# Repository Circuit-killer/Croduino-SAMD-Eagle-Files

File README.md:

# Croduino SAMD Eagle Files
## Image
will be available soon

## Description and details
Arduino compatible board based on ATSAMD21G18J with native USB. 

## Repository content
This repo contains Cadsoft Eagle .sch and .brd files for Croduino SAMD board. It also contains schematic in .pdf created from .sch Eagle file. 
Files have been arranged into folders for navigating between different versions of board. 
Tip: layer 200 shows top silkscreen and layer 208 should be bottom silkscreen. tParts and bParts layers are not used in actual PCB. 

## Docs
- available soon

## Board versions
- v1.0 - inital published version 

## License info
This product is open-source. Yay!
For any tech questions, contact us at techsupport@e-radionica.com
If you find an Issue, please open one at GitHub. If you can improve our product, fork us.

e-radionica.com Team.

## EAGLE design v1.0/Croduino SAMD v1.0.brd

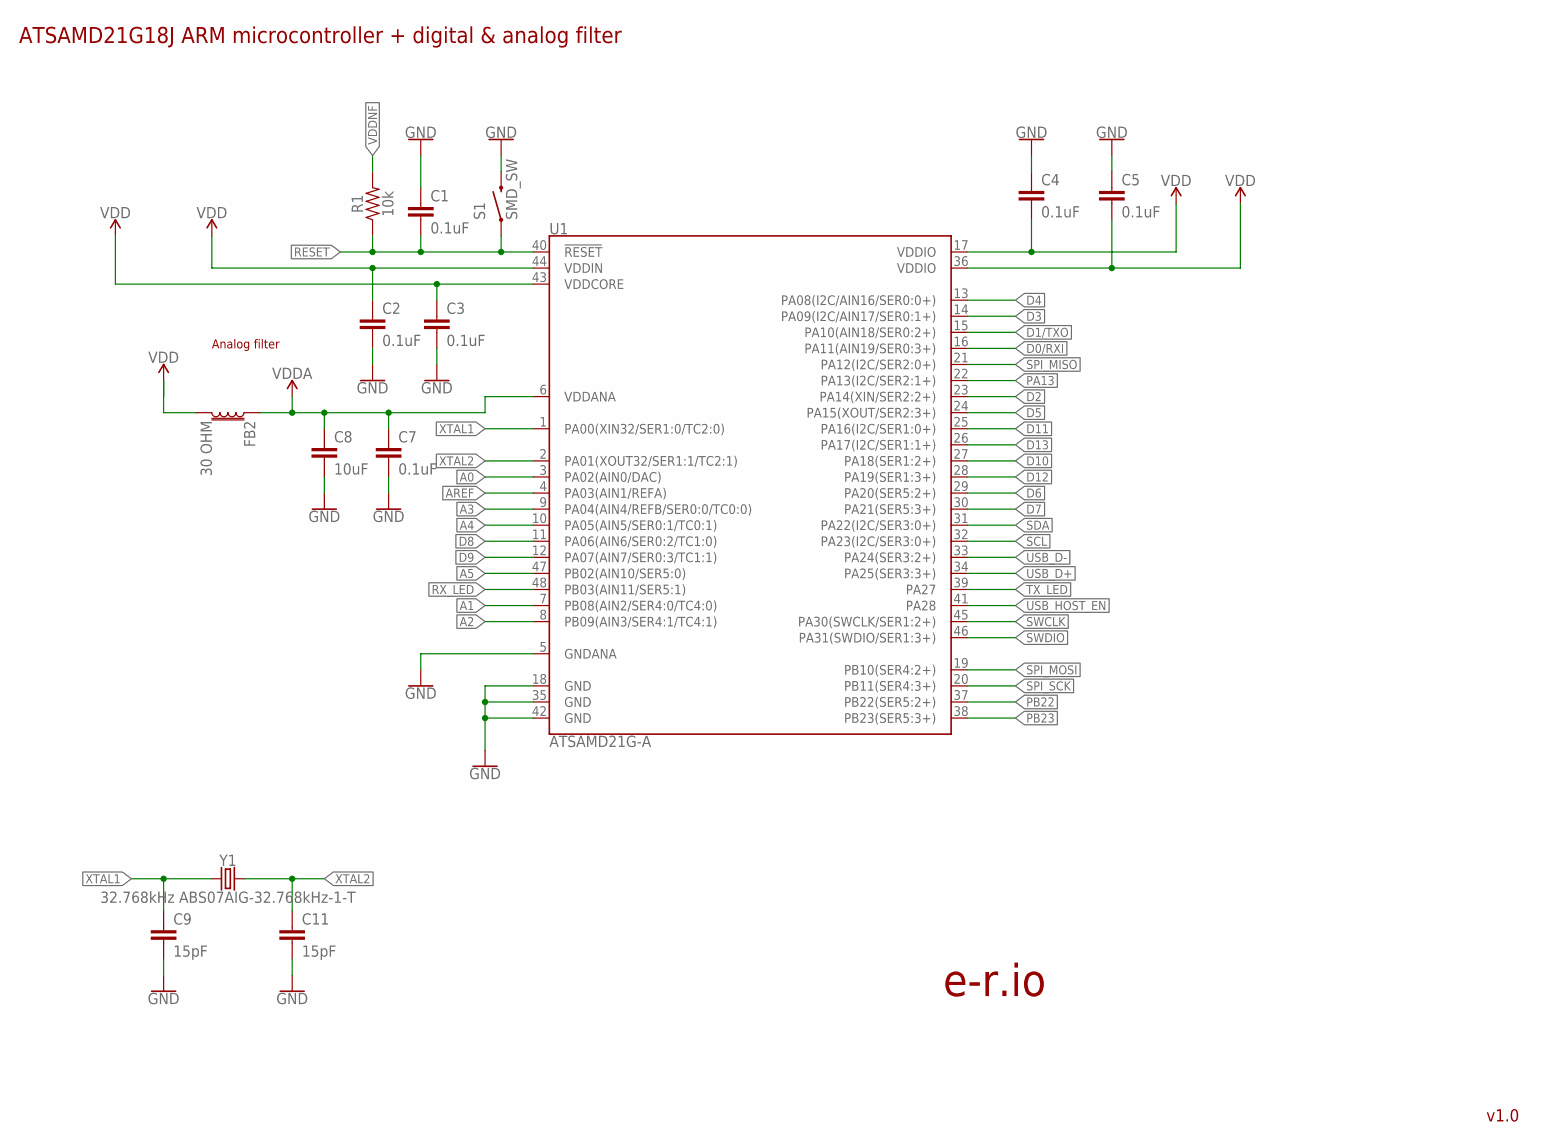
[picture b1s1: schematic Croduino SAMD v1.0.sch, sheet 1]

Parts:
C1, C2, C3, C4, C5, C7: 0.1uF; 0603
C8: 10uF; 1206
C9, C11: 15pF; 0603
FB2: 30 OHM; 0603
R1: 10k; 0603
S1: SMD_SW; TACTILE_SWITCH_SMD
U1: ATSAMD21G-A; TQFP-48
Y1: 32.768kHz ABS07AIG-32.768kHz-1-T; CRYSTAL-SMD-3.2X1.5MM

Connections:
A0: U1.3 (PA02(AIN0/DAC)); also elsewhere on the board
A1: U1.7 (PB08(AIN2/SER4:0/TC4:0)); also elsewhere on the board
A2: U1.8 (PB09(AIN3/SER4:1/TC4:1)); also elsewhere on the board
A3: U1.9 (PA04(AIN4/REFB/SER0:0/TC0:0)); also elsewhere on the board
A4: U1.10 (PA05(AIN5/SER0:1/TC0:1)); also elsewhere on the board
A5: U1.47 (PB02(AIN10/SER5:0)); also elsewhere on the board
AREF: U1.4 (PA03(AIN1/REFA)); also elsewhere on the board
D0/RXI: U1.16 (PA11(AIN19/SER0:3+)); also elsewhere on the board
D1/TXO: U1.15 (PA10(AIN18/SER0:2+)); also elsewhere on the board
D2: U1.23 (PA14(XIN/SER2:2+)); also elsewhere on the board
D3: U1.14 (PA09(I2C/AIN17/SER0:1+)); also elsewhere on the board
D4: U1.13 (PA08(I2C/AIN16/SER0:0+)); also elsewhere on the board
D5: U1.24 (PA15(XOUT/SER2:3+)); also elsewhere on the board
D6: U1.29 (PA20(SER5:2+)); also elsewhere on the board
D7: U1.30 (PA21(SER5:3+)); also elsewhere on the board
D8: U1.11 (PA06(AIN6/SER0:2/TC1:0)); also elsewhere on the board
D9: U1.12 (PA07(AIN7/SER0:3/TC1:1)); also elsewhere on the board
D10: U1.27 (PA18(SER1:2+)); also elsewhere on the board
D11: U1.25 (PA16(I2C/SER1:0+)); also elsewhere on the board
D12: U1.28 (PA19(SER1:3+)); also elsewhere on the board
D13: U1.26 (PA17(I2C/SER1:1+)); also elsewhere on the board
GND: C1.1, C2.2, C3.2, C4.1, C5.1, C7.2, C8.2, C9.2, C11.2, S1.3 (2), U1.5 (GNDANA), U1.18 (GND), U1.35 (GND), U1.42 (GND); also elsewhere on the board
PA13: U1.22 (PA13(I2C/SER2:1+)); also elsewhere on the board
PB22: U1.37 (PB22(SER5:2+)); also elsewhere on the board
PB23: U1.38 (PB23(SER5:3+)); also elsewhere on the board
RESET: C1.2, R1.1, S1.1, U1.40 (!RESET!); also elsewhere on the board
RX_LED: U1.48 (PB03(AIN11/SER5:1)); also elsewhere on the board
SCL: U1.32 (PA23(I2C/SER3:0+)); also elsewhere on the board
SDA: U1.31 (PA22(I2C/SER3:0+)); also elsewhere on the board
SPI_MISO: U1.21 (PA12(I2C/SER2:0+)); also elsewhere on the board
SPI_MOSI: U1.19 (PB10(SER4:2+)); also elsewhere on the board
SPI_SCK: U1.20 (PB11(SER4:3+)); also elsewhere on the board
SWCLK: U1.45 (PA30(SWCLK/SER1:2+)); also elsewhere on the board
SWDIO: U1.46 (PA31(SWDIO/SER1:3+)); also elsewhere on the board
TX_LED: U1.39 (PA27); also elsewhere on the board
USB_D+: U1.34 (PA25(SER3:3+)); also elsewhere on the board
USB_D-: U1.33 (PA24(SER3:2+)); also elsewhere on the board
USB_HOST_EN: U1.41 (PA28); also elsewhere on the board
VDD: C2.1, C3.1, C4.2, C5.2, FB2.2, U1.17 (VDDIO), U1.36 (VDDIO), U1.43 (VDDCORE), U1.44 (VDDIN); also elsewhere on the board
VDDA: C7.1, C8.1, FB2.1, U1.6 (VDDANA)
VDDNF: R1.2
XTAL1: C9.1, U1.1 (PA00(XIN32/SER1:0/TC2:0)), Y1.P$1 (1)
XTAL2: C11.1, U1.2 (PA01(XOUT32/SER1:1/TC2:1)), Y1.P$2 (2)

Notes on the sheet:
Analog filter
ATSAMD21G18J ARM microcontroller + digital & analog filter
e-r.io
v1.0

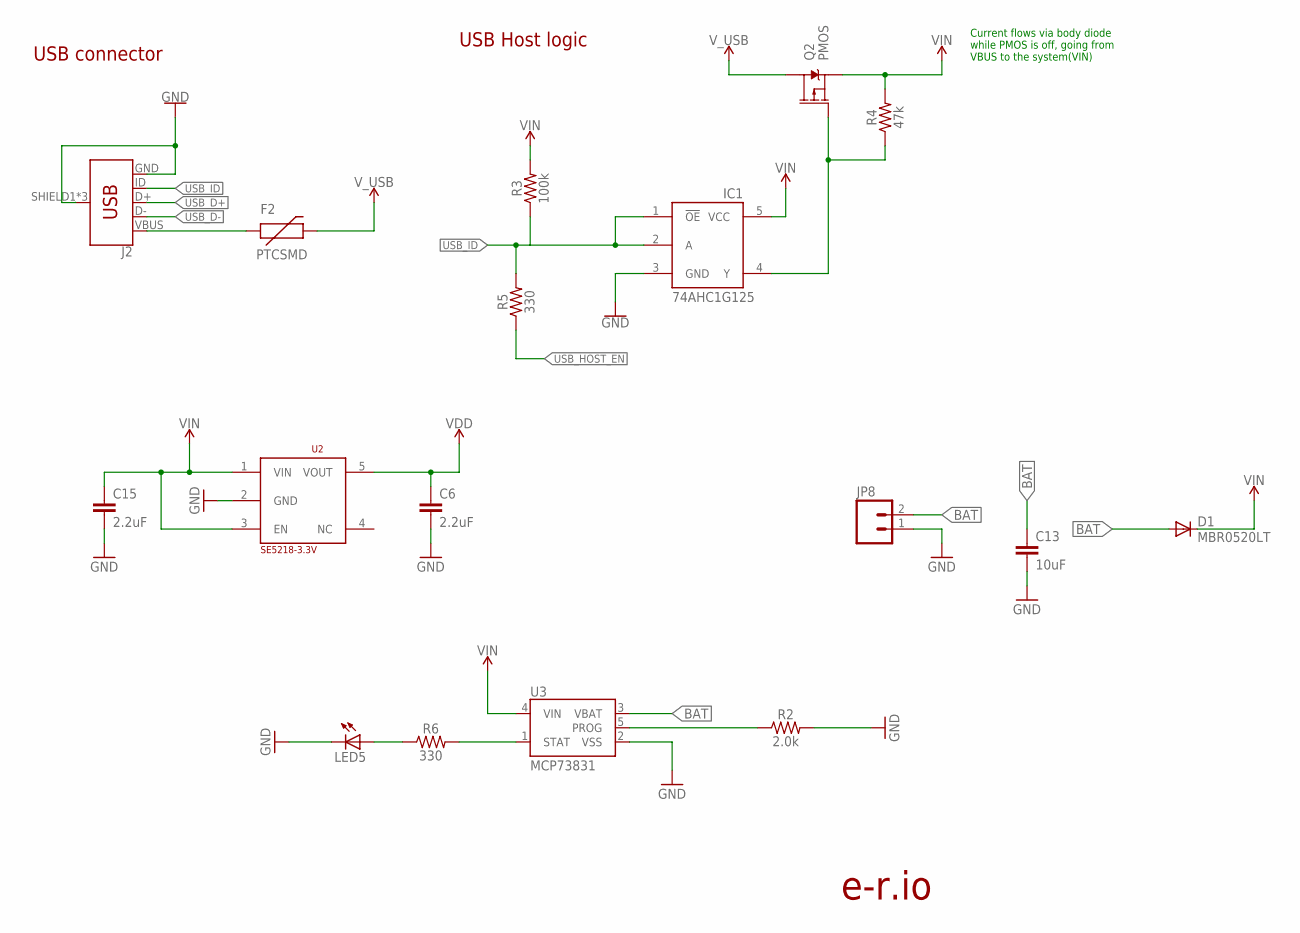
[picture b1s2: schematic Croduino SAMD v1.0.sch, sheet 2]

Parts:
C6, C15: 2.2uF; 0603
C13: 10uF; 1206
D1: MBR0520LT; SOD123
F2: PTCSMD; PTC-1206
IC1: 74AHC1G125; SOT23-5L
J2: USB_MICRO-BREDUCED_PASTE; USB-B-MICRO-SMD_RED_PASTE
JP8: M02-JST-2MM-SMT; JST-2-SMD
LED5: LEDCHIPLED_0805; CHIPLED_0805
Q2: PMOS; SOT23-3
R2: 2.0k; 0603
R3: 100k; 0603
R4: 47k; 0603
R5, R6: 330; 0603
U2: SE5218-3.3V; SOT23-5
U3: MCP73831; SOT23-5

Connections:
BAT: C13.1, D1.A, JP8.2, U3.3 (VBAT)
GND: C6.2, C13.2, C15.2, IC1.3 (GND), J2.GND, J2.SHIELD1 (SHIELD), J2.SHIELD2 (SHIELD), J2.SHIELD3 (SHIELD), JP8.1, LED5.C, R2.2, U2.2 (GND), U3.2 (VSS); also elsewhere on the board
unnamed: R6.2, U3.1 (STAT)
unnamed: F2.1, J2.VBUS
unnamed: IC1.4 (Y), Q2.1 (G), R4.1
unnamed: LED5.A, R6.1
unnamed: R2.1, U3.5 (PROG)
USB_D+: J2.D+; also elsewhere on the board
USB_D-: J2.D-; also elsewhere on the board
USB_HOST_EN: R5.1; also elsewhere on the board
USB_ID: IC1.1 (!OE), IC1.2 (A), J2.ID, R3.1, R5.2
VDD: C6.1, U2.5 (VOUT); also elsewhere on the board
VIN: C15.1, D1.C, IC1.5 (VCC), Q2.2 (S), R3.2, R4.2, U2.1 (VIN), U2.3 (EN), U3.4 (VIN); also elsewhere on the board
V_USB: F2.2, Q2.3 (D); also elsewhere on the board

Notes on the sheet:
Current flows via body diode while PMOS is off, going from VBUS to the system(VIN)
USB connector
USB Host logic
e-r.io

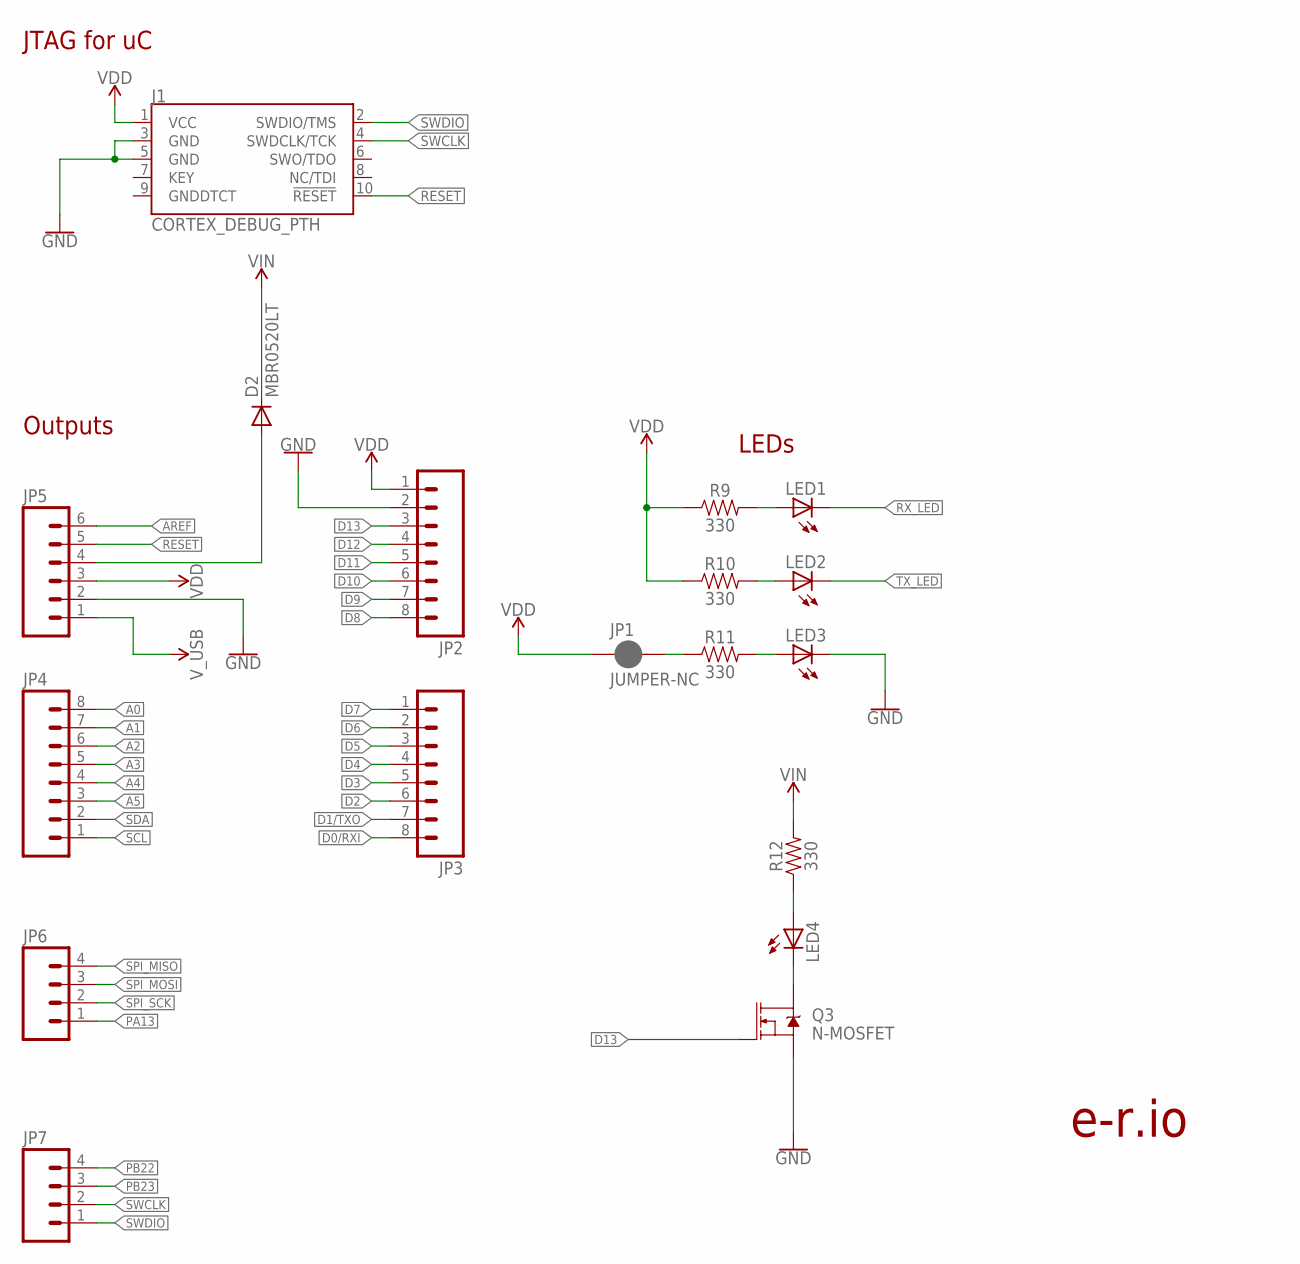
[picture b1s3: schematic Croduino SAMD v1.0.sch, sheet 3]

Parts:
D2: MBR0520LT; SOD123
J1: CORTEX_DEBUG_PTH; 2X5-PTH-1.27MM
JP1: JUMPER-NC; SMT-JUMPER_2_NC_PASTE_NO-SILK
JP2, JP3, JP4: M081X08; 1X08
JP5: M06SIP; 1X06
JP6, JP7: M04PTH; 1X04
LED1, LED2, LED3, LED4: LEDCHIPLED_0805; CHIPLED_0805
Q3: N-MOSFET; SOT23-3
R9, R10, R11, R12: 330; 0603

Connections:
A0: JP4.8; also elsewhere on the board
A1: JP4.7; also elsewhere on the board
A2: JP4.6; also elsewhere on the board
A3: JP4.5; also elsewhere on the board
A4: JP4.4; also elsewhere on the board
A5: JP4.3; also elsewhere on the board
AREF: JP5.6; also elsewhere on the board
D0/RXI: JP3.8; also elsewhere on the board
D1/TXO: JP3.7; also elsewhere on the board
D2: JP3.6; also elsewhere on the board
D3: JP3.5; also elsewhere on the board
D4: JP3.4; also elsewhere on the board
D5: JP3.3; also elsewhere on the board
D6: JP3.2; also elsewhere on the board
D7: JP3.1; also elsewhere on the board
D8: JP2.8; also elsewhere on the board
D9: JP2.7; also elsewhere on the board
D10: JP2.6; also elsewhere on the board
D11: JP2.5; also elsewhere on the board
D12: JP2.4; also elsewhere on the board
D13: JP2.3, Q3.1 (G); also elsewhere on the board
GND: J1.3 (GND), J1.5 (GND), JP2.2, JP5.2, LED3.C, Q3.2 (S); also elsewhere on the board
unnamed: JP1.2, R11.1
unnamed: LED4.A, R12.1
unnamed: D2.A, JP5.4
unnamed: LED3.A, R11.2
unnamed: LED2.A, R10.2
unnamed: LED1.A, R9.2
unnamed: LED4.C, Q3.3 (D)
PA13: JP6.1; also elsewhere on the board
PB22: JP7.4; also elsewhere on the board
PB23: JP7.3; also elsewhere on the board
RESET: J1.10 (!RESET), JP5.5; also elsewhere on the board
RX_LED: LED1.C; also elsewhere on the board
SCL: JP4.1; also elsewhere on the board
SDA: JP4.2; also elsewhere on the board
SPI_MISO: JP6.4; also elsewhere on the board
SPI_MOSI: JP6.3; also elsewhere on the board
SPI_SCK: JP6.2; also elsewhere on the board
SWCLK: J1.4 (SWDCLK/TCK), JP7.2; also elsewhere on the board
SWDIO: J1.2 (SWDIO/TMS), JP7.1; also elsewhere on the board
TX_LED: LED2.C; also elsewhere on the board
VDD: J1.1 (VCC), JP1.1, JP2.1, JP5.3, R9.1, R10.1; also elsewhere on the board
VIN: D2.C, R12.2; also elsewhere on the board
V_USB: JP5.1; also elsewhere on the board

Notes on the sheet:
JTAG for uC
Outputs
LEDs
e-r.io

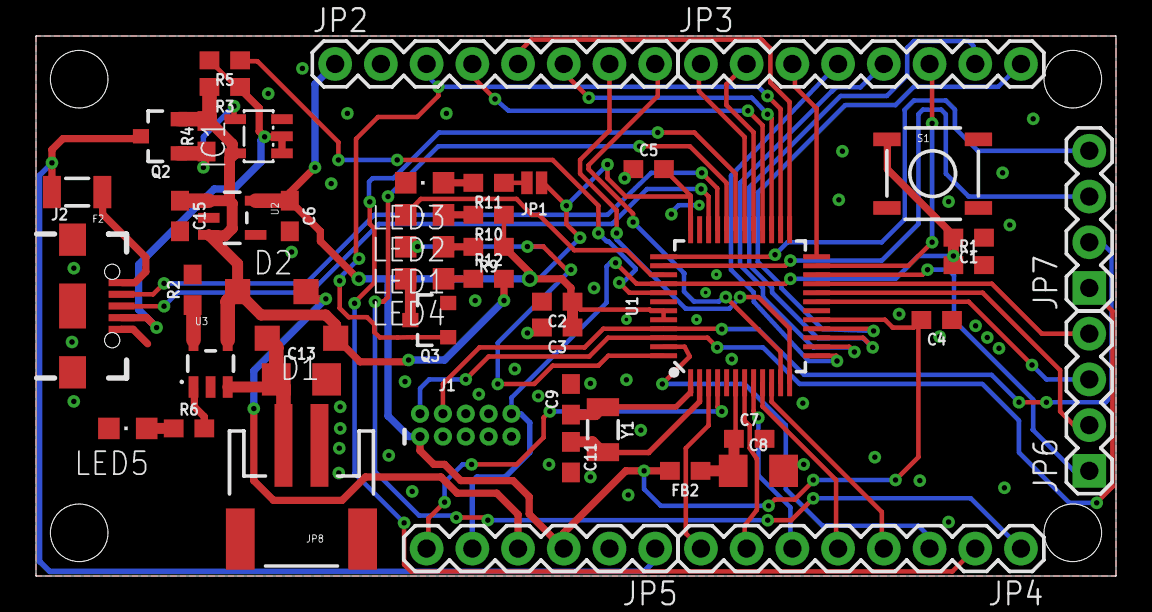
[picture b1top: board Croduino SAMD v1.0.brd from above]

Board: 2 copper layers, 60.0 x 30.0 mm, 60 parts (1 on the bottom side), 58 nets.

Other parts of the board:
U$1: SAMD-GRAFIKA
U$2: LOGO-4MM
U$3: OSH-3MM
U$4: E-R.IO-3MM
U$8: MADE-IN-CROATIA-5MM
U$9: LUDI-LOGO-24MM
U$10: SAMD-BACK
U$11: OSH-BACK-6MM
U$12: E-R.IO-6MM
U$13: LOGO-BACK-6MM
U$14: E-R.IO-BACK-12MM

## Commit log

2017-11-26 Initial
    initial

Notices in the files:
parts and their libraries:
SparkFun-Capacitors: Licensing: Creative Commons ShareAlike 4.0 International - https://creativecommons.org/licenses/by-sa/4.0
SparkFun: Licensing: CC v3.0 Share-Alike You are welcome to use this library for commercial purposes.
